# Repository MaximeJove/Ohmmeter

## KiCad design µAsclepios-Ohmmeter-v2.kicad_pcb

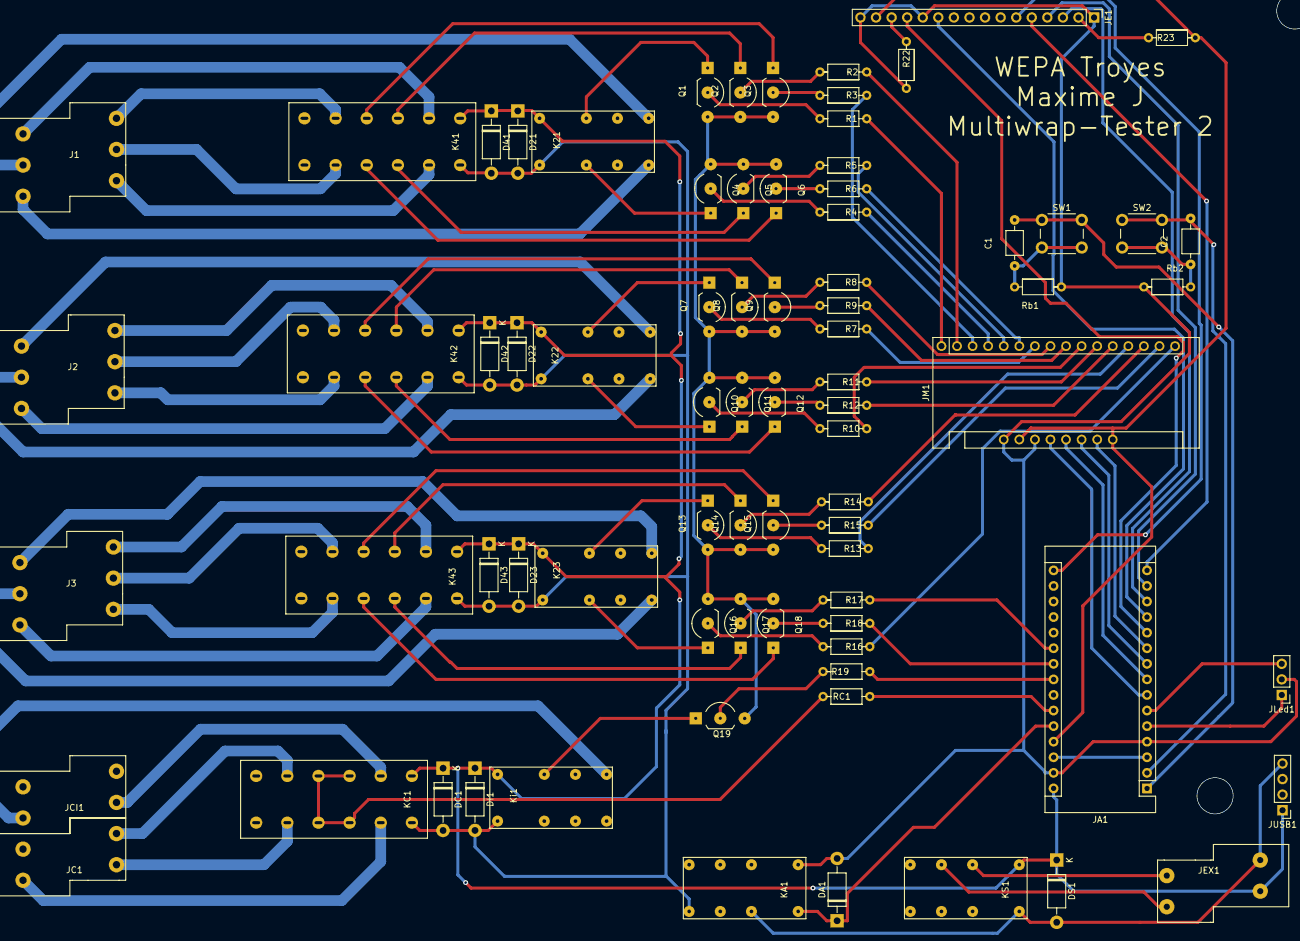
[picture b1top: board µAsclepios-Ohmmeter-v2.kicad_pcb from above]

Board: 2 copper layers, 78 parts (0 on the bottom side), 104 nets.

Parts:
C1, C2: C; Condensateur
D21, D22, D23, D41, D42, D43: 1N4007; D_DO-41_SOD81_P10.16mm_Horizontal
DA1: 1N4007; D_DO-41_SOD81_P10.16mm_Horizontal
DC1: 1N4007; D_DO-41_SOD81_P10.16mm_Horizontal
DI1: 1N4007; D_DO-41_SOD81_P10.16mm_Horizontal
DS1: 1N4007; D_DO-41_SOD81_P10.16mm_Horizontal
J1, J2, J3: MKKDS-3; MKKDS-1,5-3-5,08
JA1: Socket_Arduino; Arduino_Nano
JC1: MKKDS-2; MKKDS-1,5-2-5,08
JCI1: MKKDS-2; MKKDS-1,5-2-5,08
JE1: Socket_Ecran_1602; Socket_LCD_1602
JEX1: MKKDS-2; MKKDS-1,5-2-5,08
JLed1: rrf; PinHeader_1x03_P2.54mm_Vertical
JM1: Socket_Demux; demux
JUSB1: USB_A; PinHeader_1x04_P2.54mm_Vertical
K21, K22, K23: MT2
K41, K42, K43: S45
KA1: MT2
KC1: S45
KS1: MT2
Ki1: MT2
Q1, Q2, Q3, Q4, Q5, Q6, Q7, Q8, Q9, Q10, Q11, Q12, Q13, Q14, Q15, Q16, Q17, Q18, Q19: Q_NPN_BCE; 2N2222A
R1, R2, R3, R4, R5, R6, R7, R8, R9, R10, R11, R12, R13, R14, R15, R16, R17, R18, R19, R22, R23: R; Resistance
RC1: R; Resistance
Rb1, Rb2: R; Resistance
SW1, SW2: SW_Push; SW_PUSH_6mm_H4.3mm

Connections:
unnamed: C1.1, JA1.D1, SW1.1
unnamed: C1.2, Rb1.1, SW1.2
unnamed: C2.1, JA1.D0, SW2.1
unnamed: C2.2, Rb2.1, SW2.2
unnamed: DA1.1, JA1.A0, KA1.16
unnamed: JA1.VIN, JEX1.1, JUSB1.1
unnamed: J1.1, K41.11
unnamed: J1.2, K21.9
unnamed: J1.3, K21.8
unnamed: J1.4, K41.8
unnamed: J1.5, K41.5
unnamed: J1.6, K41.2
unnamed: J2.1, K22.9
unnamed: J2.2, K22.8
unnamed: J2.3, K42.2
unnamed: J2.4, K42.11
unnamed: J2.5, K42.8
unnamed: J2.6, K42.5
unnamed: J3.1, K23.9
unnamed: J3.2, K23.8
unnamed: J3.3, K43.2
unnamed: J3.4, K43.11
unnamed: J3.5, K43.8
unnamed: J3.6, K43.5
unnamed: JA1.5V, JE1.VDD, JM1.SIG, JM1.VCC, R23.2
unnamed: JA1.A1, RC1.1
unnamed: JA1.A3, R19.1
unnamed: JA1.A4, R18.1
unnamed: JA1.A5, R17.1
unnamed: JA1.D4, JM1.S0
unnamed: JA1.D5, JM1.S1
unnamed: JA1.D6, JM1.S2
unnamed: JA1.D7, JM1.S3
unnamed: JA1.D8, JE1.RS
unnamed: JA1.D9, JE1.E
unnamed: JA1.D10, JE1.D7
unnamed: JA1.D11, JE1.D6
unnamed: JA1.D12, JE1.D5
unnamed: JA1.D13, JE1.D4
unnamed: JC1.2, KC1.2
unnamed: JC1.3, KC1.8
unnamed: JC1.4, KC1.5
unnamed: JCI1.2, Ki1.9
unnamed: JCI1.4, KC1.11
unnamed: JE1.A, R23.1
unnamed: JE1.V0, R22.1
unnamed: JEX1.3, KS1.6
unnamed: JEX1.4, KS1.4
unnamed: JM1.C0, R1.1
unnamed: JM1.C1, R2.1
unnamed: JM1.C2, R3.1
unnamed: JM1.C3, R4.1
unnamed: JM1.C4, R5.1
unnamed: JM1.C5, R6.1
unnamed: JM1.C6, R7.1
unnamed: JM1.C7, R8.1
unnamed: JM1.C8, R9.1
unnamed: JM1.C9, R10.1
unnamed: JM1.C10, R11.1
unnamed: JM1.C11, R12.1
unnamed: JM1.C12, R13.1
unnamed: JM1.C13, R14.1
unnamed: JM1.C14, R15.1
unnamed: JM1.C15, R16.1
unnamed: K21.4, Q4.3
unnamed: K21.13, Q1.3
unnamed: K22.4, Q10.3
unnamed: K22.13, Q7.3
unnamed: K23.4, Q16.3
unnamed: K23.13, Q13.3
unnamed: K41.3, Q5.3
unnamed: K41.4, Q6.3
unnamed: K41.9, Q3.3
unnamed: K41.10, Q2.3
unnamed: K42.3, Q11.3
unnamed: K42.4, Q12.3
unnamed: K42.9, Q9.3
unnamed: K42.10, Q8.3
unnamed: K43.3, Q17.3
unnamed: K43.4, Q18.3
unnamed: K43.9, Q15.3
unnamed: K43.10, Q14.3
unnamed: KC1.3, KC1.4, KC1.9, KC1.10, RC1.2
unnamed: Ki1.13, Q19.3
unnamed: Q1.1, R1.2
unnamed: Q1.2, Q2.2, Q3.2, Q4.2, Q5.2, Q6.2, Q7.2, Q8.2, Q9.2, Q10.2, Q11.2, Q12.2, Q13.2, Q14.2, Q15.2, Q16.2, Q17.2, Q18.2, Q19.2
unnamed: Q2.1, R2.2
unnamed: Q3.1, R3.2
unnamed: Q4.1, R4.2
unnamed: Q5.1, R5.2
unnamed: Q6.1, R6.2
unnamed: Q7.1, R7.2
unnamed: Q8.1, R8.2
unnamed: Q9.1, R9.2
unnamed: Q10.1, R10.2
unnamed: Q11.1, R11.2
unnamed: Q12.1, R12.2
unnamed: Q13.1, R13.2
unnamed: Q14.1, R14.2
unnamed: Q15.1, R15.2
unnamed: Q16.1, R16.2
unnamed: Q17.1, R17.2
unnamed: Q18.1, R18.2
unnamed: Q19.1, R19.2

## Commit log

2021-05-28 Ohmmeter v2.0 ( sans récupération de l'information d'urgence
